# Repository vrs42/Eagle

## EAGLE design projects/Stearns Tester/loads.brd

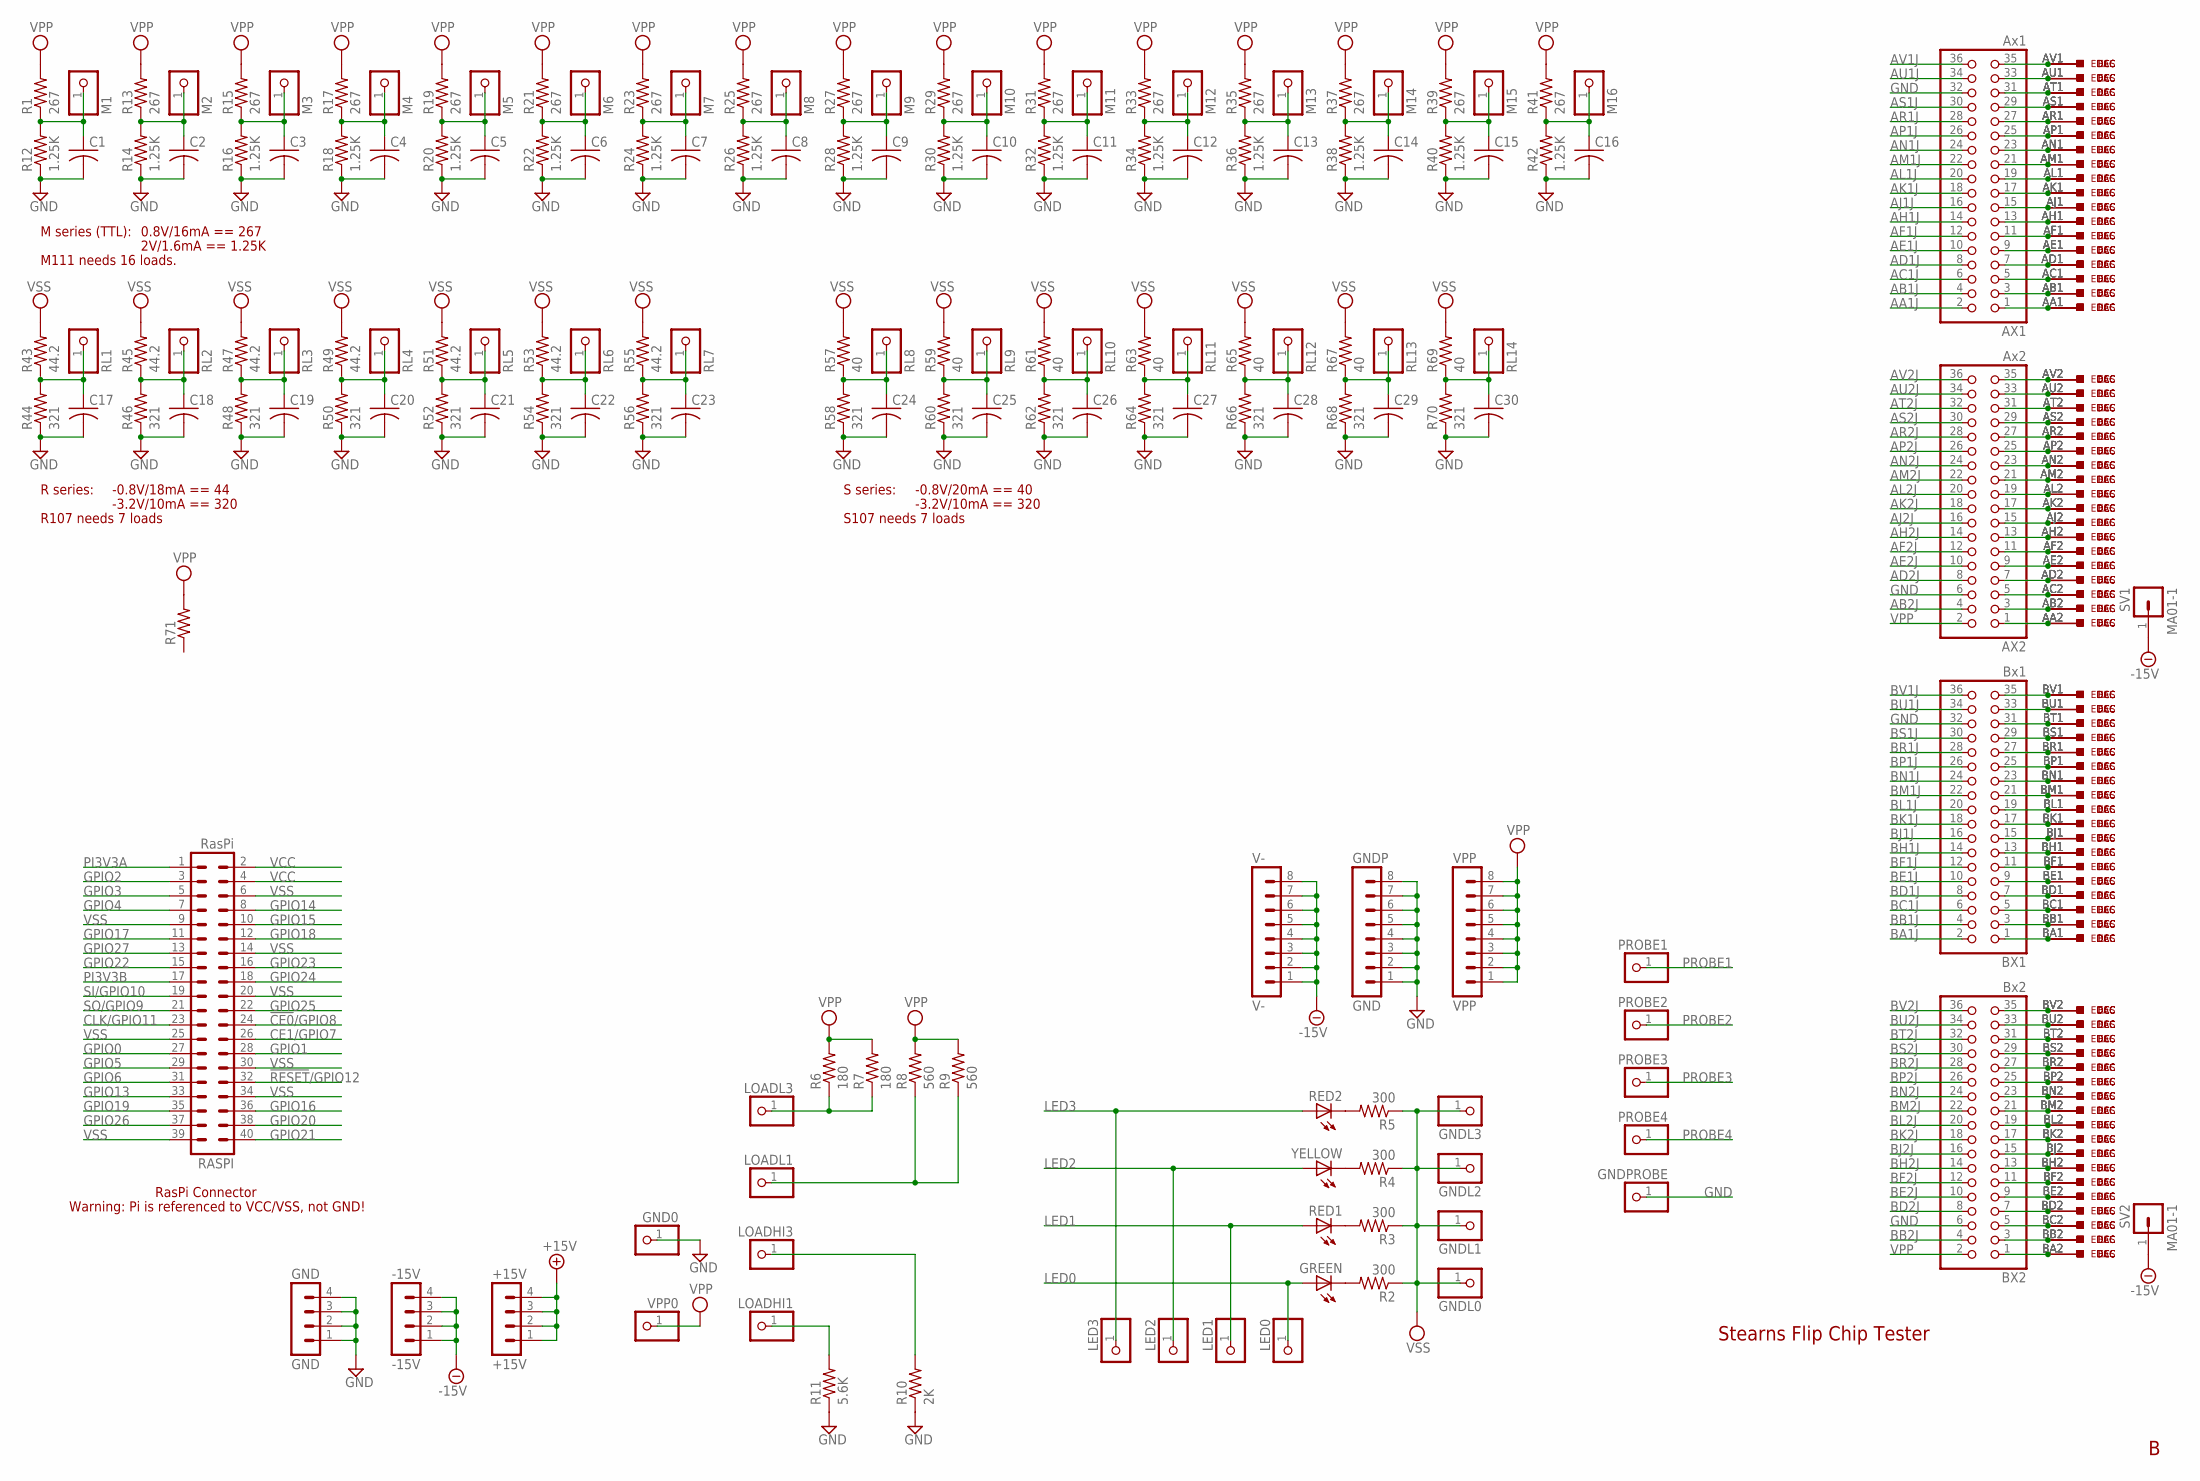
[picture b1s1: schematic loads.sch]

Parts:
+15V: +15V; MA04-1
-15V: -15V; MA04-1
AX1: Ax1; 2X18
AX2: Ax2; 2X18
BX1: Bx1; 2X18
BX2: Bx2; 2X18
C1, C2, C3, C4, C5, C6, C7, C8, C9, C10, C11, C12, C13, C14, C15, C16, C17, C18, C19, C20, C21, C22, C23, C24, C25, C26, C27, C28, C29, C30: C-US025-025X050; C025-025X050
DEC: W971; H807-2
ECS: W971ECS; ECS2418-2
EDAC: W971EDAC; EDAC346-36-2
GND: GND; MA04-1
GND0: PINHD-1X1; 1X01
GNDL0, GNDL1, GNDL2, GNDL3: PINHD-1X1; 1X01
GNDP: GND; MA08-1
GNDPROBE: PINHD-1X1; 1X01
GREEN: LED5MM
LED0, LED1, LED2, LED3: PINHD-1X1; 1X01
LOADHI1, LOADHI3: PINHD-1X1; 1X01
LOADL1, LOADL3: PINHD-1X1; 1X01
M1, M2, M3, M4, M5, M6, M7, M8, M9, M10, M11, M12, M13, M14, M15, M16: PINHD-1X1; 1X01
PROBE1, PROBE2, PROBE3, PROBE4: PINHD-1X1; 1X01
R1, R13, R15, R17, R19, R21, R23, R25, R27, R29, R31, R33, R35, R37, R39, R41: 267; 0207/10
R2, R3, R4, R5: 300; 0207/10
R6, R7: 180; 0207/10
R8, R9: 560; 0207/10
R10: 2K; 0207/10
R11: 5.6K; 0207/10
R12, R14, R16, R18, R20, R22, R24, R26, R28, R30, R32, R34, R36, R38, R40, R42: 1.25K; 0207/10
R43, R45, R47, R49, R51, R53, R55: 44.2; 0207/10
R44, R46, R48, R50, R52, R54, R56, R58, R60, R62, R64, R66, R68, R70: 321; 0207/10
R57, R59, R61, R63, R65, R67, R69: 40; 0207/10
R71: R-US_0207/10; 0207/10
RASPI: RasPi; MA20-2
RED1, RED2: LED5MM
RL1, RL2, RL3, RL4, RL5, RL6, RL7, RL8, RL9, RL10, RL11, RL12, RL13, RL14: PINHD-1X1; 1X01
SV1, SV2: MA01-1
V-: V-; MA08-1
VPP: VPP; MA08-1
VPP0: PINHD-1X1; 1X01
YELLOW: LED5MM

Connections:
!CE0!/GPIO8: RASPI.24
!RESET!/GPIO12: RASPI.32
+15V: +15V.1, +15V.2, +15V.3, +15V.4
-15V: -15V.1, -15V.2, -15V.3, -15V.4, SV1.1, SV2.1, V-.1, V-.2, V-.3, V-.4, V-.5, V-.6, V-.7, V-.8
AA1J: AX1.2
AB1J: AX1.4
AB2J: AX2.4
AC1J: AX1.6
AD1J: AX1.8
AD2J: AX2.8
AE1J: AX1.10
AE2J: AX2.10
AF1J: AX1.12
AF2J: AX2.12
AH1J: AX1.14
AH2J: AX2.14
AJ1J: AX1.16
AJ2J: AX2.16
AK1J: AX1.18
AK2J: AX2.18
AL1J: AX1.20
AL2J: AX2.20
AM1J: AX1.22
AM2J: AX2.22
AN1J: AX1.24
AN2J: AX2.24
AP1J: AX1.26
AP2J: AX2.26
AR1J: AX1.28
AR2J: AX2.28
AS1J: AX1.30
AS2J: AX2.30
AT2J: AX2.32
AU1J: AX1.34
AU2J: AX2.34
AV1J: AX1.36
AV2J: AX2.36
BA1J: BX1.2
BB1J: BX1.4
BB2J: BX2.4
BC1J: BX1.6
BD1J: BX1.8
BD2J: BX2.8
BE1J: BX1.10
BE2J: BX2.10
BF1J: BX1.12
BF2J: BX2.12
BH1J: BX1.14
BH2J: BX2.14
BJ1J: BX1.16
BJ2J: BX2.16
BK1J: BX1.18
BK2J: BX2.18
BL1J: BX1.20
BL2J: BX2.20
BM1J: BX1.22
BM2J: BX2.22
BN1J: BX1.24
BN2J: BX2.24
BP1J: BX1.26
BP2J: BX2.26
BR1J: BX1.28
BR2J: BX2.28
BS1J: BX1.30
BS2J: BX2.30
BT2J: BX2.32
BU1J: BX1.34
BU2J: BX2.34
BV1J: BX1.36
BV2J: BX2.36
CE1/GPIO7: RASPI.26
CLK/GPIO11: RASPI.23
GND: AX1.32, AX2.6, BX1.32, BX2.6, C1.2, C2.2, C3.2, C4.2, C5.2, C6.2, C7.2, C8.2, C9.2, C10.2, C11.2, C12.2, C13.2, C14.2, C15.2, C16.2, C17.2, C18.2, C19.2, C20.2, C21.2, C22.2, C23.2, C24.2, C25.2, C26.2, C27.2, C28.2, C29.2, C30.2, GND.1, GND.2, GND.3, GND.4, GND0.1, GNDP.1, GNDP.2, GNDP.3, GNDP.4, GNDP.5, GNDP.6, GNDP.7, GNDP.8, GNDPROBE.1, R10.1, R11.1, R12.1, R14.1, R16.1, R18.1, R20.1, R22.1, R24.1, R26.1, R28.1, R30.1, R32.1, R34.1, R36.1, R38.1, R40.1, R42.1, R44.1, R46.1, R48.1, R50.1, R52.1, R54.1, R56.1, R58.1, R60.1, R62.1, R64.1, R66.1, R68.1, R70.1
GPIO0: RASPI.27
GPIO1: RASPI.28
GPIO2: RASPI.3
GPIO3: RASPI.5
GPIO4: RASPI.7
GPIO5: RASPI.29
GPIO6: RASPI.31
GPIO13: RASPI.33
GPIO14: RASPI.8
GPIO15: RASPI.10
GPIO16: RASPI.36
GPIO17: RASPI.11
GPIO18: RASPI.12
GPIO19: RASPI.35
GPIO20: RASPI.38
GPIO21: RASPI.40
GPIO22: RASPI.15
GPIO23: RASPI.16
GPIO24: RASPI.18
GPIO25: RASPI.22
GPIO26: RASPI.37
GPIO27: RASPI.13
LED0: GREEN.A, LED0.1
LED1: LED1.1, RED1.A
LED2: LED2.1, YELLOW.A
LED3: LED3.1, RED2.A
unnamed: AX1.1, DEC.AA1, ECS.AA1, EDAC.AA1
unnamed: AX1.35, DEC.AV1, ECS.AV1, EDAC.AV1
unnamed: AX1.33, DEC.AU1, ECS.AU1, EDAC.AU1
unnamed: AX1.31, DEC.AT1, ECS.AT1, EDAC.AT1
unnamed: AX1.29, DEC.AS1, ECS.AS1, EDAC.AS1
unnamed: AX1.27, DEC.AR1, ECS.AR1, EDAC.AR1
unnamed: AX1.25, DEC.AP1, ECS.AP1, EDAC.AP1
unnamed: AX1.23, DEC.AN1, ECS.AN1, EDAC.AN1
unnamed: AX1.21, DEC.AM1, ECS.AM1, EDAC.AM1
unnamed: AX1.19, DEC.AL1, ECS.AL1, EDAC.AL1
unnamed: AX1.17, DEC.AK1, ECS.AK1, EDAC.AK1
unnamed: AX1.15, DEC.AJ1, ECS.AJ1, EDAC.AJ1
unnamed: AX1.13, DEC.AH1, ECS.AH1, EDAC.AH1
unnamed: AX1.11, DEC.AF1, ECS.AF1, EDAC.AF1
unnamed: AX1.9, DEC.AE1, ECS.AE1, EDAC.AE1
unnamed: AX1.7, DEC.AD1, ECS.AD1, EDAC.AD1
unnamed: AX1.5, DEC.AC1, ECS.AC1, EDAC.AC1
unnamed: AX1.3, DEC.AB1, ECS.AB1, EDAC.AB1
unnamed: AX2.1, DEC.AA2, ECS.AA2, EDAC.AA2
unnamed: AX2.3, DEC.AB2, ECS.AB2, EDAC.AB2
unnamed: AX2.5, DEC.AC2, ECS.AC2, EDAC.AC2
unnamed: AX2.7, DEC.AD2, ECS.AD2, EDAC.AD2
unnamed: AX2.9, DEC.AE2, ECS.AE2, EDAC.AE2
unnamed: AX2.11, DEC.AF2, ECS.AF2, EDAC.AF2
unnamed: AX2.13, DEC.AH2, ECS.AH2, EDAC.AH2
unnamed: AX2.15, DEC.AJ2, ECS.AJ2, EDAC.AJ2
unnamed: AX2.17, DEC.AK2, ECS.AK2, EDAC.AK2
unnamed: AX2.19, DEC.AL2, ECS.AL2, EDAC.AL2
unnamed: AX2.21, DEC.AM2, ECS.AM2, EDAC.AM2
unnamed: AX2.23, DEC.AN2, ECS.AN2, EDAC.AN2
unnamed: AX2.25, DEC.AP2, ECS.AP2, EDAC.AP2
unnamed: AX2.27, DEC.AR2, ECS.AR2, EDAC.AR2
unnamed: AX2.29, DEC.AS2, ECS.AS2, EDAC.AS2
unnamed: AX2.31, DEC.AT2, ECS.AT2, EDAC.AT2
unnamed: AX2.33, DEC.AU2, ECS.AU2, EDAC.AU2
unnamed: AX2.35, DEC.AV2, ECS.AV2, EDAC.AV2
unnamed: BX2.1, DEC.BA2, ECS.BA2, EDAC.BA2
unnamed: BX2.3, DEC.BB2, ECS.BB2, EDAC.BB2
unnamed: BX2.5, DEC.BC2, ECS.BC2, EDAC.BC2
unnamed: BX2.7, DEC.BD2, ECS.BD2, EDAC.BD2
unnamed: BX2.9, DEC.BE2, ECS.BE2, EDAC.BE2
unnamed: BX2.11, DEC.BF2, ECS.BF2, EDAC.BF2
unnamed: BX2.13, DEC.BH2, ECS.BH2, EDAC.BH2
unnamed: BX2.15, DEC.BJ2, ECS.BJ2, EDAC.BJ2
unnamed: BX2.17, DEC.BK2, ECS.BK2, EDAC.BK2
unnamed: BX2.19, DEC.BL2, ECS.BL2, EDAC.BL2
unnamed: BX2.21, DEC.BM2, ECS.BM2, EDAC.BM2
unnamed: BX2.23, DEC.BN2, ECS.BN2, EDAC.BN2
unnamed: BX2.25, DEC.BP2, ECS.BP2, EDAC.BP2
unnamed: BX2.27, DEC.BR2, ECS.BR2, EDAC.BR2
unnamed: BX2.29, DEC.BS2, ECS.BS2, EDAC.BS2
unnamed: BX2.31, DEC.BT2, ECS.BT2, EDAC.BT2
unnamed: BX2.33, DEC.BU2, ECS.BU2, EDAC.BU2
unnamed: BX2.35, DEC.BV2, ECS.BV2, EDAC.BV2
unnamed: BX1.1, DEC.BA1, ECS.BA1, EDAC.BA1
unnamed: BX1.3, DEC.BB1, ECS.BB1, EDAC.BB1
unnamed: BX1.5, DEC.BC1, ECS.BC1, EDAC.BC1
unnamed: BX1.7, DEC.BD1, ECS.BD1, EDAC.BD1
unnamed: BX1.9, DEC.BE1, ECS.BE1, EDAC.BE1
unnamed: BX1.11, DEC.BF1, ECS.BF1, EDAC.BF1
unnamed: BX1.13, DEC.BH1, ECS.BH1, EDAC.BH1
unnamed: BX1.15, DEC.BJ1, ECS.BJ1, EDAC.BJ1
unnamed: BX1.17, DEC.BK1, ECS.BK1, EDAC.BK1
unnamed: BX1.19, DEC.BL1, ECS.BL1, EDAC.BL1
unnamed: BX1.21, DEC.BM1, ECS.BM1, EDAC.BM1
unnamed: BX1.23, DEC.BN1, ECS.BN1, EDAC.BN1
unnamed: BX1.25, DEC.BP1, ECS.BP1, EDAC.BP1
unnamed: BX1.27, DEC.BR1, ECS.BR1, EDAC.BR1
unnamed: BX1.29, DEC.BS1, ECS.BS1, EDAC.BS1
unnamed: BX1.31, DEC.BT1, ECS.BT1, EDAC.BT1
unnamed: BX1.33, DEC.BU1, ECS.BU1, EDAC.BU1
unnamed: BX1.35, DEC.BV1, ECS.BV1, EDAC.BV1
unnamed: GREEN.K (C), R2.2
unnamed: R3.2, RED1.K (C)
unnamed: R4.2, YELLOW.K (C)
unnamed: R5.2, RED2.K (C)
unnamed: LOADL3.1, R6.1, R7.1
unnamed: LOADL1.1, R8.1, R9.1
unnamed: LOADHI1.1, R11.2
unnamed: LOADHI3.1, R10.2
unnamed: C1.1, M1.1, R1.1, R12.2
unnamed: C2.1, M2.1, R13.1, R14.2
unnamed: C3.1, M3.1, R15.1, R16.2
unnamed: C4.1, M4.1, R17.1, R18.2
unnamed: C5.1, M5.1, R19.1, R20.2
unnamed: C6.1, M6.1, R21.1, R22.2
unnamed: C7.1, M7.1, R23.1, R24.2
unnamed: C8.1, M8.1, R25.1, R26.2
unnamed: C9.1, M9.1, R27.1, R28.2
unnamed: C10.1, M10.1, R29.1, R30.2
unnamed: C11.1, M11.1, R31.1, R32.2
unnamed: C12.1, M12.1, R33.1, R34.2
unnamed: C13.1, M13.1, R35.1, R36.2
unnamed: C14.1, M14.1, R37.1, R38.2
unnamed: C15.1, M15.1, R39.1, R40.2
unnamed: C16.1, M16.1, R41.1, R42.2
unnamed: C17.1, R43.1, R44.2, RL1.1
unnamed: C18.1, R45.1, R46.2, RL2.1
unnamed: C19.1, R47.1, R48.2, RL3.1
unnamed: C20.1, R49.1, R50.2, RL4.1
unnamed: C21.1, R51.1, R52.2, RL5.1
unnamed: C22.1, R53.1, R54.2, RL6.1
unnamed: C23.1, R55.1, R56.2, RL7.1
unnamed: C24.1, R57.1, R58.2, RL8.1
unnamed: C25.1, R59.1, R60.2, RL9.1
unnamed: C26.1, R61.1, R62.2, RL10.1
unnamed: C27.1, R63.1, R64.2, RL11.1
unnamed: C28.1, R65.1, R66.2, RL12.1
unnamed: C29.1, R67.1, R68.2, RL13.1
unnamed: C30.1, R69.1, R70.2, RL14.1
PI3V3A: RASPI.1
PI3V3B: RASPI.17
PROBE1: PROBE1.1
PROBE2: PROBE2.1
PROBE3: PROBE3.1
PROBE4: PROBE4.1
SI/GPIO10: RASPI.19
SO/GPIO9: RASPI.21
VCC: RASPI.2, RASPI.4
VPP: AX2.2, BX2.2, R1.2, R6.2, R7.2, R8.2, R9.2, R13.2, R15.2, R17.2, R19.2, R21.2, R23.2, R25.2, R27.2, R29.2, R31.2, R33.2, R35.2, R37.2, R39.2, R41.2, R71.2, VPP.1, VPP.2, VPP.3, VPP.4, VPP.5, VPP.6, VPP.7, VPP.8, VPP0.1
VSS: GNDL0.1, GNDL1.1, GNDL2.1, GNDL3.1, R2.1, R3.1, R4.1, R5.1, R43.2, R45.2, R47.2, R49.2, R51.2, R53.2, R55.2, R57.2, R59.2, R61.2, R63.2, R65.2, R67.2, R69.2, RASPI.6, RASPI.9, RASPI.14, RASPI.20, RASPI.25, RASPI.30, RASPI.34, RASPI.39

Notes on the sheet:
Stearns Flip Chip Tester
RasPi Connector
Warning: Pi is referenced to VCC/VSS, not GND!
M series (TTL):
2V/1.6mA == 1.25K
0.8V/16mA == 267
M111 needs 16 loads.
R series:
R107 needs 7 loads
-0.8V/18mA == 44
-3.2V/10mA == 320
S series:
S107 needs 7 loads
-0.8V/20mA == 40

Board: 2 copper layers, 170 parts (0 on the bottom side), 120 nets, no tracks yet.

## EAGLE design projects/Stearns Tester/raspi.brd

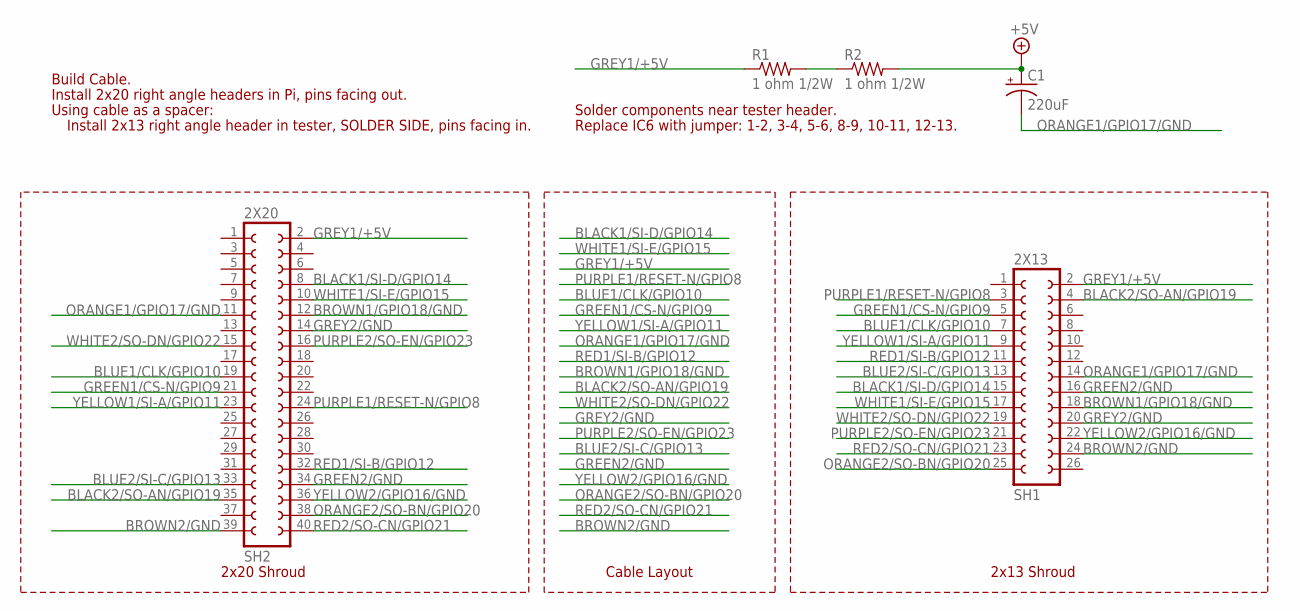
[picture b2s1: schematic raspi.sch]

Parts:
C1: 220uF; E15-6
R1, R2: 1 ohm 1/2W; 0207/10
SH1: 2X13; FE13-2
SH2: 2X20; FE20-2

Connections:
+5V: C1.+, R2.2
BLACK1/SI-D/GPIO14: SH1.15, SH2.8
BLACK2/SO-AN/GPIO19: SH1.4, SH2.35
BLUE1/CLK/GPIO10: SH1.7, SH2.19
BLUE2/SI-C/GPIO13: SH1.13, SH2.33
BROWN1/GPIO18/GND: SH1.18, SH2.12
BROWN2/GND: SH1.24, SH2.39
GREEN1/CS-N/GPIO9: SH1.5, SH2.21
GREEN2/GND: SH1.16, SH2.34
GREY1/+5V: R1.1, SH1.2, SH2.2
GREY2/GND: SH1.20, SH2.14
unnamed: R1.2, R2.1
ORANGE1/GPIO17/GND: C1.-, SH1.14, SH2.11
ORANGE2/SO-BN/GPIO20: SH1.25, SH2.38
PURPLE1/RESET-N/GPIO8: SH1.3, SH2.24
PURPLE2/SO-EN/GPIO23: SH1.21, SH2.16
RED1/SI-B/GPIO12: SH1.11, SH2.32
RED2/SO-CN/GPIO21: SH1.23, SH2.40
WHITE1/SI-E/GPIO15: SH1.17, SH2.10
WHITE2/SO-DN/GPIO22: SH1.19, SH2.15
YELLOW1/SI-A/GPIO11: SH1.9, SH2.23
YELLOW2/GPIO16/GND: SH1.22, SH2.36

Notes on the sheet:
Replace IC6 with jumper: 1-2, 3-4, 5-6, 8-9, 10-11, 12-13.
Cable Layout
2x20 Shroud
2x13 Shroud
Solder components near tester header.
Build Cable.
Using cable as a spacer:
Install 2x13 right angle header in tester, SOLDER SIDE, pins facing in.
Install 2x20 right angle headers in Pi, pins facing out.

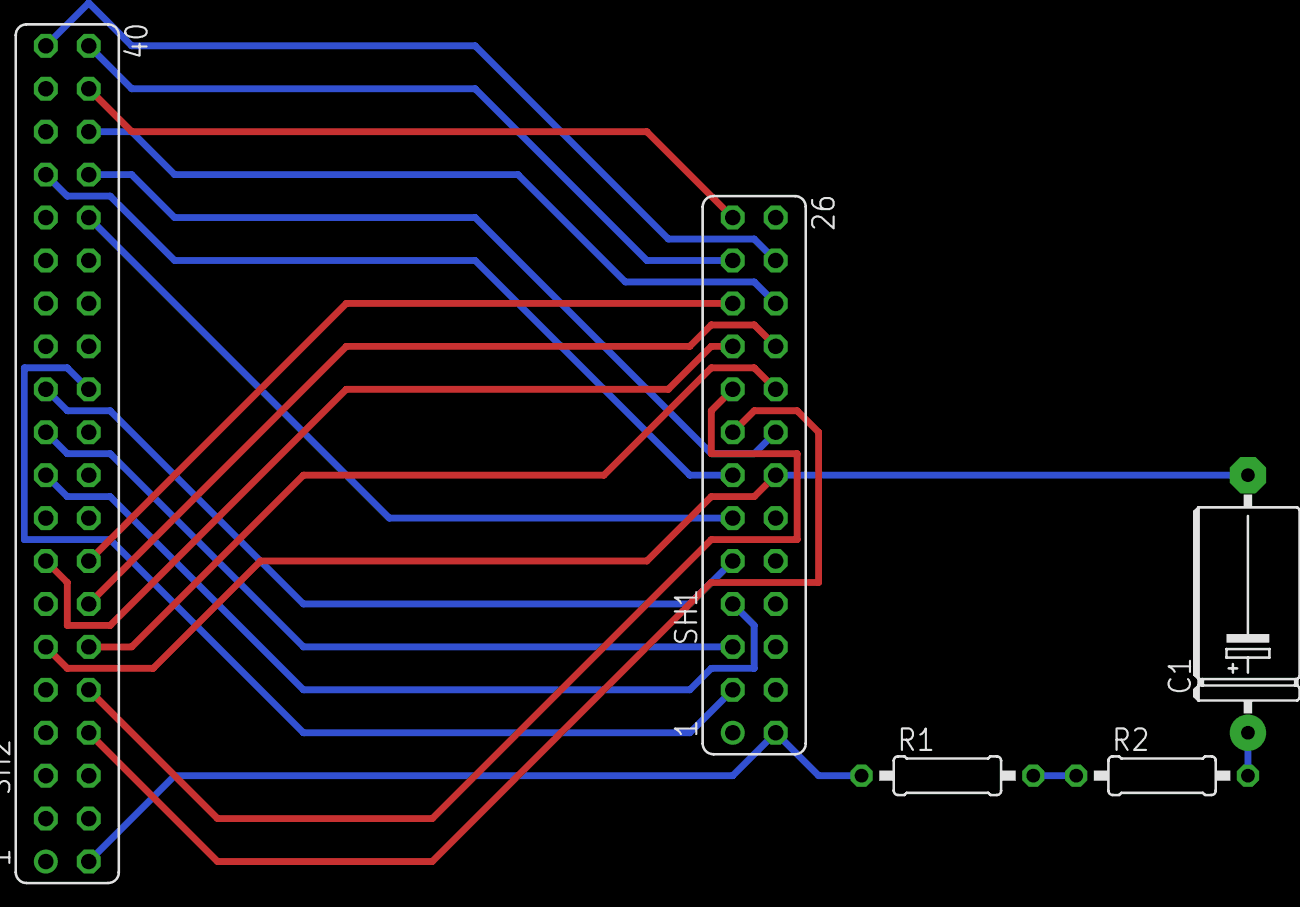
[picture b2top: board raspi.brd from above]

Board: 3 copper layers, 5 parts (0 on the bottom side), 22 nets.

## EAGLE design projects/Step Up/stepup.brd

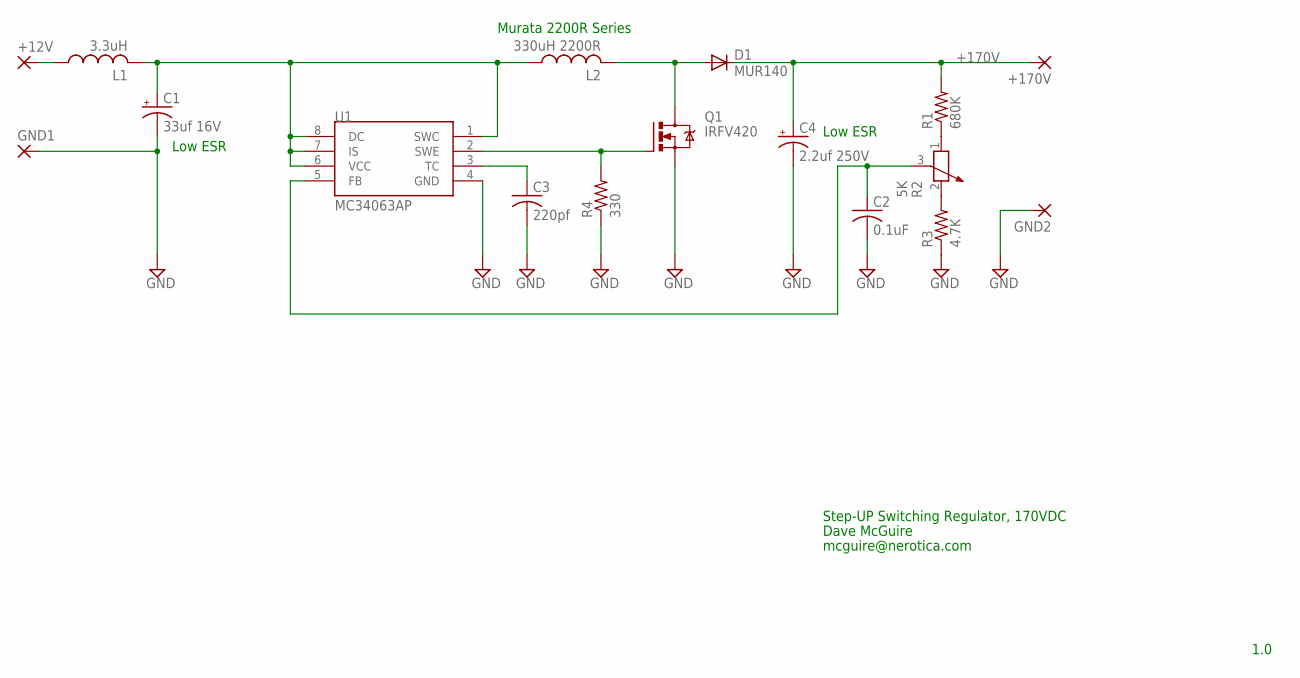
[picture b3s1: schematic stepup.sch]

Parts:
+12V, +170V: 2,54/0,9
C1: 33uf 16V; E2,5-6E
C2: 0.1uF; C050-025X075
C3: 220pf; C050-025X075
C4: 2.2uf 250V; E2,5-6E
D1: MUR140; DO41-10
GND1, GND2: 2,54/0,9
L1: 3.3uH; 0207/10
L2: 330uH 2200R; 0207/10
Q1: IRFV420; TO220BV
R1: 680K; 0207/10
R2: 5K; PT-10S
R3: 4.7K; 0207/10
R4: 330; 0207/10
U1: MC34063AP; DIL08

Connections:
+170V: +170V.1, C4.+, D1.C, R1.2
GND: C1.-, C2.2, C3.2, C4.-, GND1.1, GND2.1, Q1.S, R3.1, R4.1, U1.4 (GND)
unnamed: C1.+, L1.2, L2.1, U1.1 (SWC), U1.6 (VCC), U1.7 (IS), U1.8 (DC)
unnamed: C3.1, U1.3 (TC)
unnamed: Q1.G, R4.2, U1.2 (SWE)
unnamed: C2.1, R2.3, U1.5 (FB)
unnamed: D1.A, L2.2, Q1.D
unnamed: R2.2, R3.2
unnamed: R1.1, R2.1
unnamed: +12V.1, L1.1

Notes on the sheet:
Low ESR
Murata 2200R Series
Step-UP Switching Regulator, 170VDC
1.0
Dave McGuire
mcguire@nerotica.com

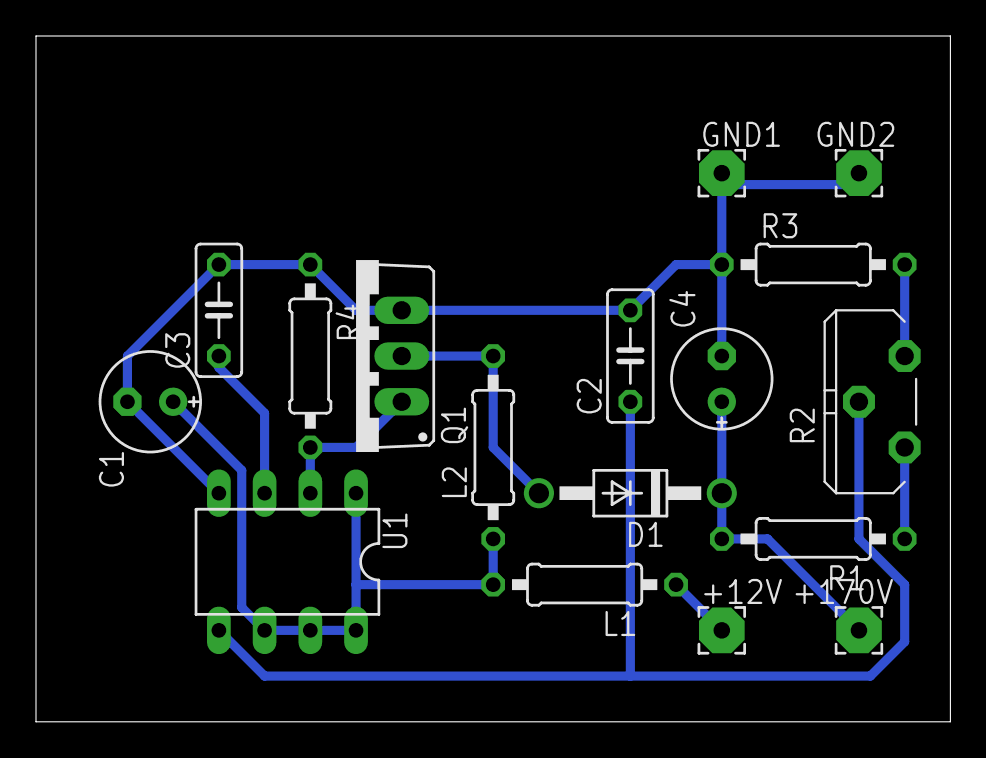
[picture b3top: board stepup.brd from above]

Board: 2 copper layers, 50.8 x 38.1 mm, 17 parts (0 on the bottom side), 10 nets.

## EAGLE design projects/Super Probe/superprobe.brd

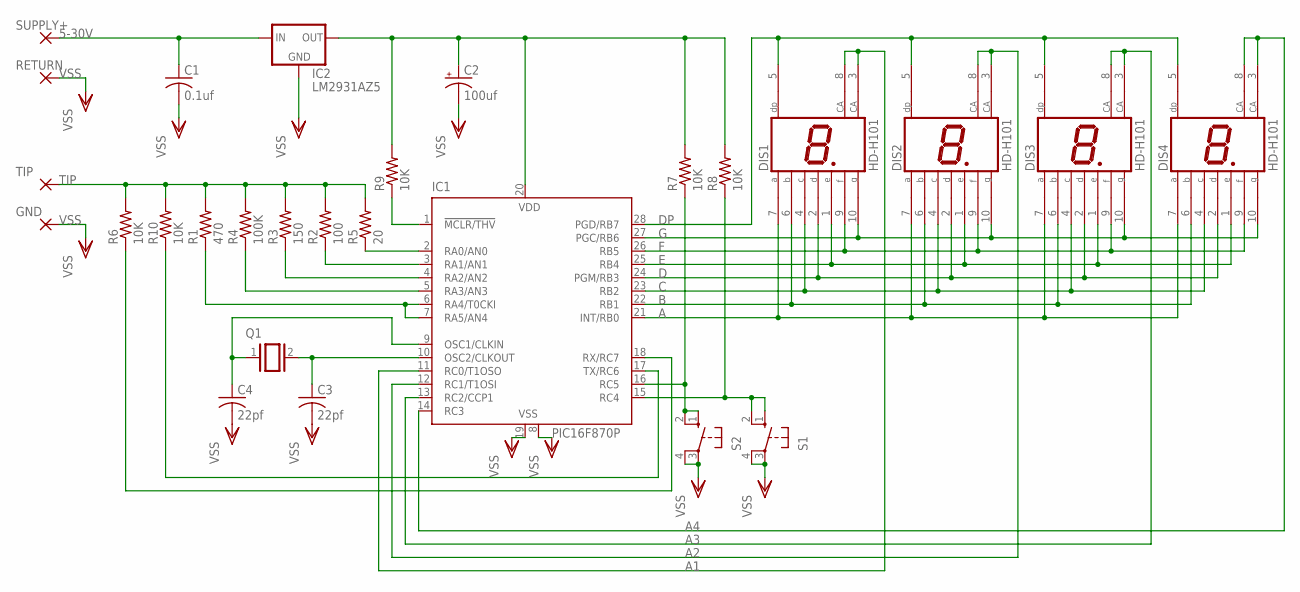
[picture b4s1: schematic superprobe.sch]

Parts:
C1: 0.1uf; C050-025X075
C2: 100uf; E15-6
C3, C4: 22pf; C050-025X075
DIS1, DIS2, DIS3, DIS4: HD-H101; HDSP-M
GND: PAD-0520; 0520
IC1: PIC16F870P; DIL28-3
IC2: LM2931AZ5; TO92
Q1: XTAL/S; QS
R1: 470; 0207/10
R2: 100; 0207/10
R3: 150; 0207/10
R4: 100K; 0207/10
R5: 20; 0207/10
R6, R7, R8, R9, R10: 10K; 0207/10
RETURN: PAD-0520; 0520
S1, S2: 40-XX; B3F-40XX
SUPPLY+: PAD-0520; 0520
TIP: PAD-0520; 0520

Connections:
5-30V: C1.1, IC2.1 (IN), SUPPLY+.P$1
A: DIS1.7 (A), DIS2.7 (A), DIS3.7 (A), DIS4.7 (A), IC1.21 (INT/RB0)
A1: DIS1.3 (CA), DIS1.8 (CA), IC1.11 (RC0/T1OSO)
A2: DIS2.3 (CA), DIS2.8 (CA), IC1.12 (RC1/T1OSI)
A3: DIS3.3 (CA), DIS3.8 (CA), IC1.13 (RC2/CCP1)
A4: DIS4.3 (CA), DIS4.8 (CA), IC1.14 (RC3)
B: DIS1.6 (B), DIS2.6 (B), DIS3.6 (B), DIS4.6 (B), IC1.22 (RB1)
C: DIS1.4 (C), DIS2.4 (C), DIS3.4 (C), DIS4.4 (C), IC1.23 (RB2)
D: DIS1.2 (D), DIS2.2 (D), DIS3.2 (D), DIS4.2 (D), IC1.24 (PGM/RB3)
DP: DIS1.5 (DP), DIS2.5 (DP), DIS3.5 (DP), DIS4.5 (DP), IC1.28 (PGD/RB7)
E: DIS1.1 (E), DIS2.1 (E), DIS3.1 (E), DIS4.1 (E), IC1.25 (RB4)
F: DIS1.9 (F), DIS2.9 (F), DIS3.9 (F), DIS4.9 (F), IC1.26 (RB5)
G: DIS1.10 (G), DIS2.10 (G), DIS3.10 (G), DIS4.10 (G), IC1.27 (PGC/RB6)
unnamed: IC1.1 (!MCLR/THV), R9.1
unnamed: IC1.2 (RA0/AN0), R5.1
unnamed: IC1.6 (RA4/T0CKI), IC1.7 (RA5/AN4), R1.1
unnamed: IC1.5 (RA3/AN3), R4.1
unnamed: IC1.4 (RA2/AN2), R3.1
unnamed: IC1.3 (RA1/AN1), R2.1
unnamed: IC1.16 (RC5), R7.1, S2.1 (S), S2.2 (S1)
unnamed: IC1.15 (RC4), R8.1, S1.1 (S), S1.2 (S1)
unnamed: IC1.18 (RX/RC7), R6.1
unnamed: IC1.17 (TX/RC6), R10.1
unnamed: C4.1, IC1.9 (OSC1/CLKIN), Q1.1
unnamed: C3.1, IC1.10 (OSC2/CLKOUT), Q1.2
TIP: R1.2, R2.2, R3.2, R4.2, R5.2, R6.2, R10.2, TIP.P$1
VDD: C2.+, IC1.20 (VDD), IC2.3 (OUT), R7.2, R8.2, R9.2
VSS: C1.2, C2.-, C3.2, C4.2, GND.P$1, IC1.8 (VSS), IC1.19 (VSS), IC2.2 (GND), RETURN.P$1, S1.3, S1.4 (P1), S2.3, S2.4 (P1)

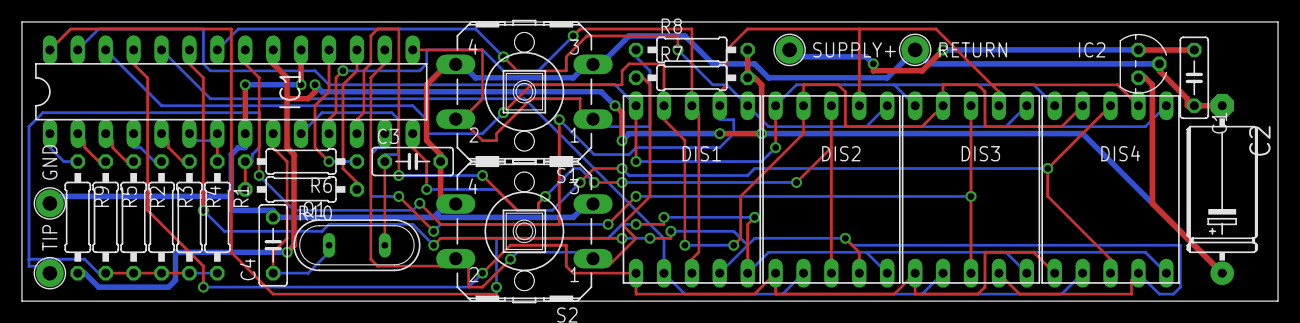
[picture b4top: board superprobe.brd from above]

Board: 2 copper layers, 114.3 x 25.4 mm, 27 parts (0 on the bottom side), 28 nets.

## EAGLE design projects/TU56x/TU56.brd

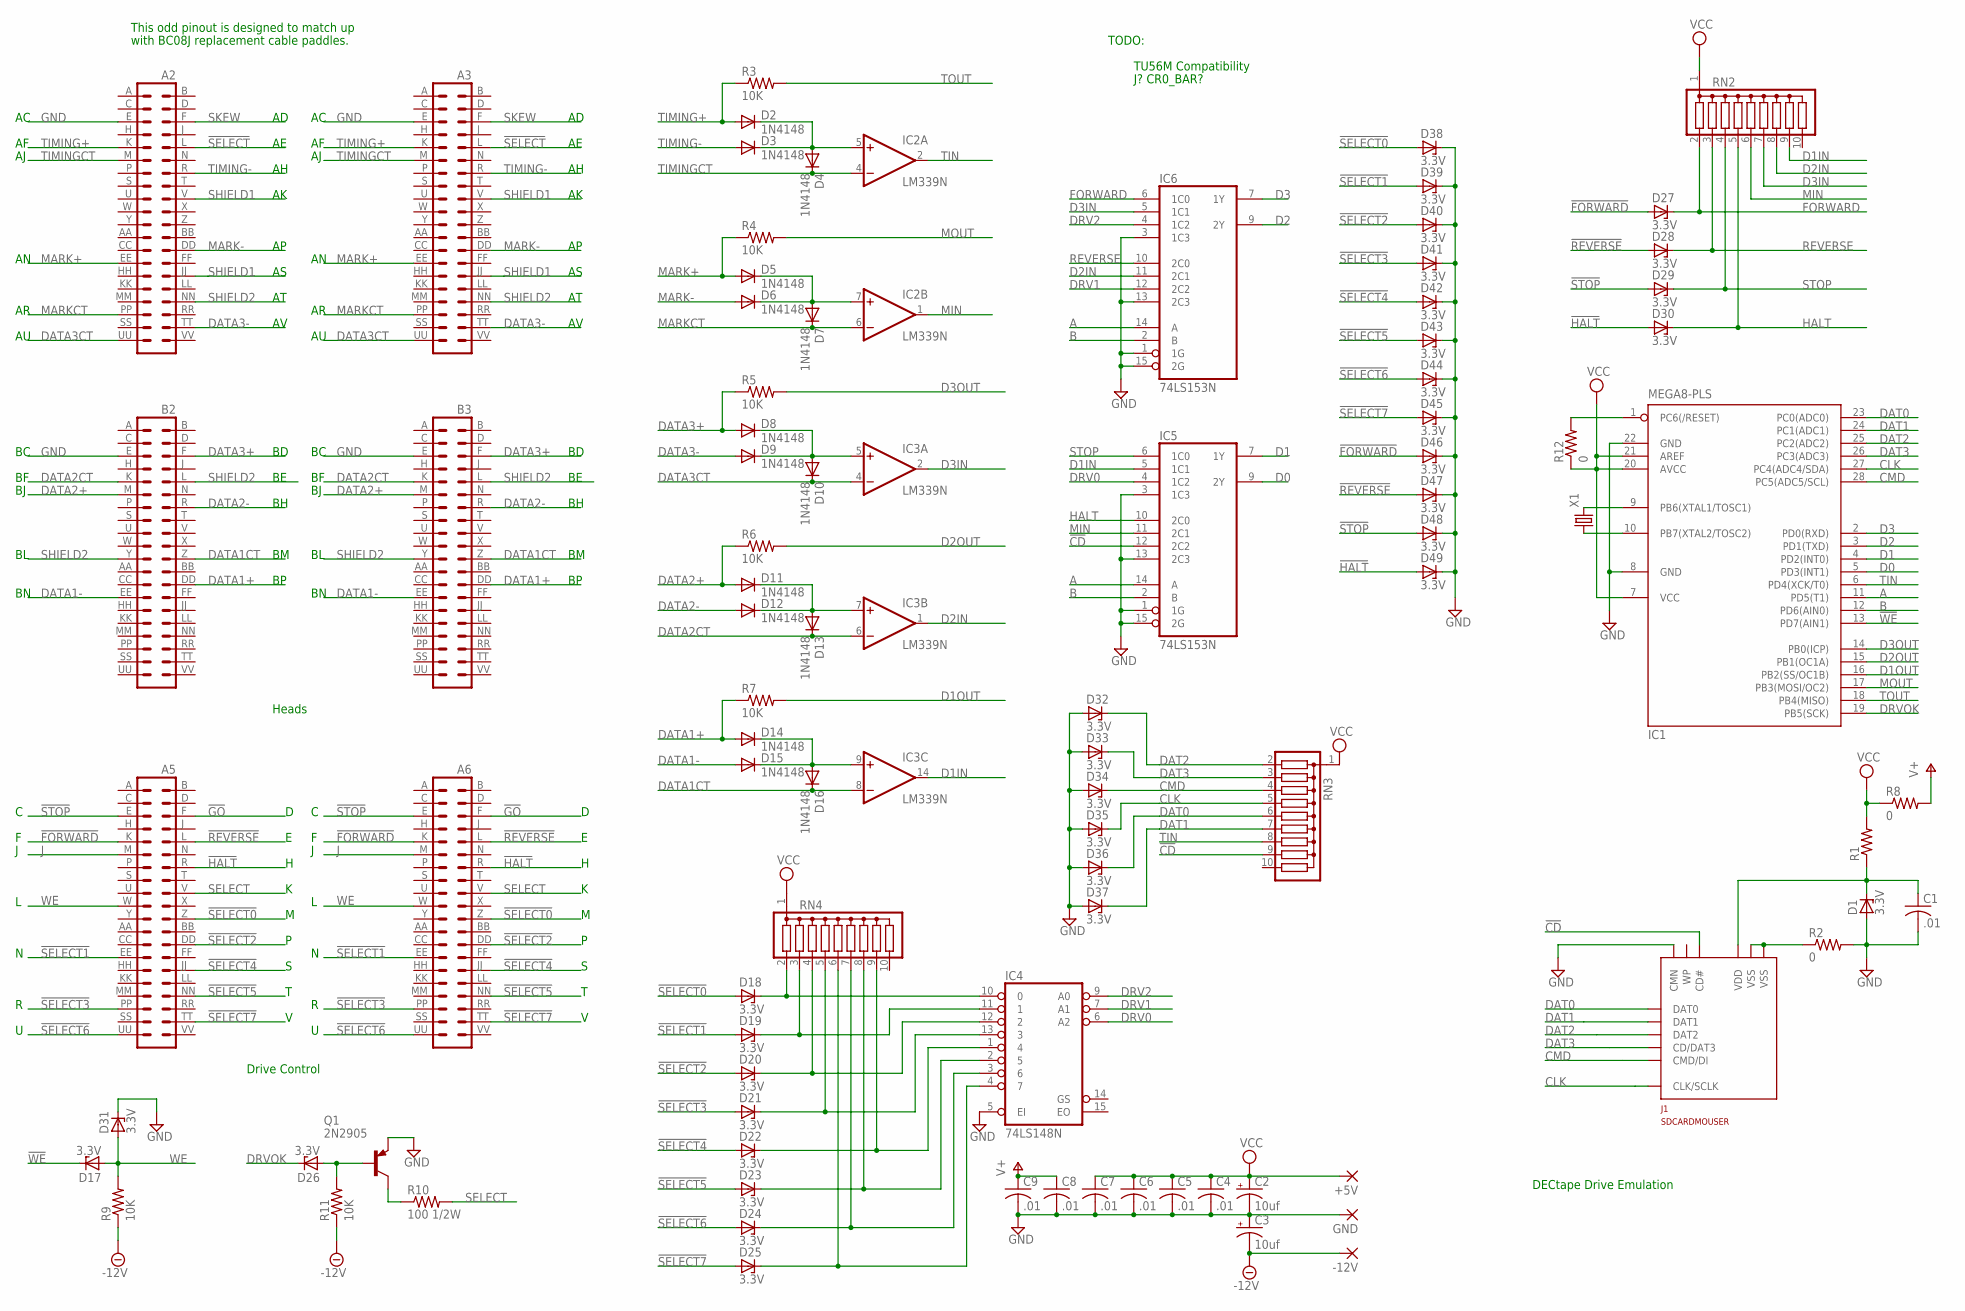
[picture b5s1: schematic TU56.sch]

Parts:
+5V: 2,15/1,0
-12V: 2,15/1,0
A2, A3, A5, A6: DEC40PINV
B2, B3: DEC40PINV
C1, C4, C5, C6, C7, C8, C9: .01; C050-025X075
C2, C3: 10uf; E2,5-7
D1, D17, D18, D19, D20, D21, D22, D23, D24, D25, D26, D27, D28, D29, D30, D31, D32, D33, D34, D35, D36, D37, D38, D39, D40, D41, D42, D43, D44, D45, D46, D47, D48, D49: 3.3V; DO35Z10
D2, D3, D4, D5, D6, D7, D8, D9, D10, D11, D12, D13, D14, D15, D16: 1N4148; DO35-10
GND: 2,15/1,0
IC1: MEGA8-PLS; DIL28-3
IC2, IC3: LM339N; DIL14
IC4: 74LS148N; DIL16
IC5, IC6: 74LS153N; DIL16
J1: SDCARDMOUSER; SCDA1A
Q1: 2N2905; TO5
R1: R-US_0207/10; 0207/10
R2, R8, R12: 0; 0207/10
R3, R4, R5, R6, R7, R9, R11: 10K; 0207/10
R10: 100 1/2W; 0309V
RN2, RN3, RN4: G09R; SIL10
X1: CRYSTALHC49S; HC49/S

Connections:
!CD: IC5.12 (2C2), J1.10 (CD#), RN3.9
!FORWARD: A5.K (9), A6.K (9), D27.A, D46.A
!GO: A5.F (6), A6.F (6)
!HALT: A5.R (14), A6.R (14), D30.A, D49.A
!REVERSE: A5.L (10), A6.L (10), D28.A, D47.A
!SELECT: A2.L (10), A3.L (10)
!SELECT0: A5.Z (22), A6.Z (22), D18.A, D38.A
!SELECT1: A5.EE (27), A6.EE (27), D19.A, D39.A
!SELECT2: A5.DD (26), A6.DD (26), D20.A, D40.A
!SELECT3: A5.PP (35), A6.PP (35), D21.A, D41.A
!SELECT4: A5.JJ (30), A6.JJ (30), D22.A, D42.A
!SELECT5: A5.NN (34), A6.NN (34), D23.A, D43.A
!SELECT6: A5.UU (39), A6.UU (39), D24.A, D44.A
!SELECT7: A5.TT (38), A6.TT (38), D25.A, D45.A
!STOP: A5.E (5), A6.E (5), D29.A, D48.A
!WE: D17.C, IC1.13 (PD7(AIN1))
-12V: -12V.1, C3.-, R9.1, R11.1
A: IC1.11 (PD5(T1)), IC5.14 (A), IC6.14 (A)
B: IC1.12 (PD6(AIN0)), IC5.2 (B), IC6.2 (B)
CLK: D35.C, IC1.27 (PC4(ADC4/SDA)), J1.5 (CLK/SCLK), RN3.5
CMD: D34.C, IC1.28 (PC5(ADC5/SCL)), J1.2 (CMD/DI), RN3.4
D0: IC1.5 (PD3(INT1)), IC5.9 (2Y)
D1: IC1.4 (PD2(INT0)), IC5.7 (1Y)
D1IN: IC3.14 (OUT), IC5.5 (1C1), RN2.9
D1OUT: IC1.16 (PB2(SS/OC1B)), R7.2
D2: IC1.3 (PD1(TXD)), IC6.9 (2Y)
D2IN: IC3.1 (OUT), IC6.11 (2C1), RN2.8
D2OUT: IC1.15 (PB1(OC1A)), R6.2
D3: IC1.2 (PD0(RXD)), IC6.7 (1Y)
D3IN: IC3.2 (OUT), IC6.5 (1C1), RN2.7
D3OUT: IC1.14 (PB0(ICP)), R5.2
DAT0: D36.C, IC1.23 (PC0(ADC0)), J1.7 (DAT0), RN3.6
DAT1: D37.C, IC1.24 (PC1(ADC1)), J1.8 (DAT1), RN3.7
DAT2: D32.C, IC1.25 (PC2(ADC2)), J1.9 (DAT2), RN3.2
DAT3: D33.C, IC1.26 (PC3(ADC3)), J1.1 (CD/DAT3), RN3.3
DATA1+: B2.DD (26), B3.DD (26), D14.A, R7.1
DATA1-: B2.EE (27), B3.EE (27), D15.A
DATA1CT: B2.Z (22), B3.Z (22), D16.C, IC3.8 (-IN)
DATA2+: B2.M (11), B3.M (11), D11.A, R6.1
DATA2-: B2.R (14), B3.R (14), D12.A
DATA2CT: B2.K (9), B3.K (9), D13.C, IC3.6 (-IN)
DATA3+: B2.F (6), B3.F (6), D8.A, R5.1
DATA3-: A2.TT (38), A3.TT (38), D9.A
DATA3CT: A2.UU (39), A3.UU (39), D10.C, IC3.4 (-IN)
DRV0: IC4.6 (A2), IC5.4 (1C2)
DRV1: IC4.7 (A1), IC6.12 (2C2)
DRV2: IC4.9 (A0), IC6.4 (1C2)
DRVOK: D26.C, IC1.19 (PB5(SCK))
FORWARD: D27.C, IC6.6 (1C0), RN2.2
GND: A2.E (5), A3.E (5), B2.E (5), B3.E (5), C1.2, C2.-, C3.+, C4.2, C5.2, C6.2, C7.2, C8.2, C9.2, D1.A, D31.C, D32.A, D33.A, D34.A, D35.A, D36.A, D37.A, D38.C, D39.C, D40.C, D41.C, D42.C, D43.C, D44.C, D45.C, D46.C, D47.C, D48.C, D49.C, GND.1, IC1.8 (GND), IC1.22 (GND), IC2.12 (GND), IC3.12 (GND), IC4.5 (EI), IC4.8 (GND), IC5.1 (1G), IC5.3 (1C3), IC5.8 (GND), IC5.13 (2C3), IC5.15 (2G), IC6.1 (1G), IC6.3 (1C3), IC6.8 (GND), IC6.13 (2C3), IC6.15 (2G), J1.11 (CMN), J1.13 (GND), J1.14 (GND), Q1.1 (E), R2.2
HALT: D30.C, IC5.10 (2C0), RN2.5
J: A5.M (11), A6.M (11)
MARK+: A2.EE (27), A3.EE (27), D5.A, R4.1
MARK-: A2.DD (26), A3.DD (26), D6.A
MARKCT: A2.PP (35), A3.PP (35), D7.C, IC2.6 (-IN)
MIN: IC2.1 (OUT), IC5.11 (2C1), RN2.6
MOUT: IC1.17 (PB3(MOSI/OC2)), R4.2
unnamed: IC1.10 (PB7(XTAL2/TOSC2)), X1.1
unnamed: IC1.9 (PB6(XTAL1/TOSC1)), X1.2
unnamed: D18.C, IC4.10 (0), RN4.2
unnamed: D19.C, IC4.11 (1), RN4.3
unnamed: D20.C, IC4.12 (2), RN4.4
unnamed: D2.C, D3.C, D4.A, IC2.5 (+IN)
unnamed: D21.C, IC4.13 (3), RN4.5
unnamed: D22.C, IC4.1 (4), RN4.9
unnamed: D23.C, IC4.2 (5), RN4.8
unnamed: D5.C, D6.C, D7.A, IC2.7 (+IN)
unnamed: D8.C, D9.C, D10.A, IC3.5 (+IN)
unnamed: D11.C, D12.C, D13.A, IC3.7 (+IN)
unnamed: D14.C, D15.C, D16.A, IC3.9 (+IN)
unnamed: D24.C, IC4.3 (6), RN4.7
unnamed: D25.C, IC4.4 (7), RN4.6
unnamed: IC1.1 (PC6(/RESET)), R12.2
unnamed: Q1.3 (C), R10.1
unnamed: D26.A, Q1.2 (B), R11.2
REVERSE: D28.C, IC6.10 (2C0), RN2.3
SELECT: A5.V (18), A6.V (18), R10.2
SHIELD1: A2.JJ (30), A2.V (18), A3.JJ (30), A3.V (18)
SHIELD2: A2.NN (34), A3.NN (34), B2.L (10), B2.Y (21), B3.L (10), B3.Y (21)
SKEW: A2.F (6), A3.F (6)
STOP: D29.C, IC5.6 (1C0), RN2.4
TIMING+: A2.K (9), A3.K (9), D2.A, R3.1
TIMING-: A2.R (14), A3.R (14), D3.A
TIMINGCT: A2.M (11), A3.M (11), D4.C, IC2.4 (-IN)
TIN: IC1.6 (PD4(XCK/T0)), IC2.2 (OUT), RN3.8
TOUT: IC1.18 (PB4(MISO)), R3.2
V+: C8.1, C9.1, IC2.3 (V+), IC3.3 (V+), R8.2
VCC: +5V.1, C2.+, C4.1, C5.1, C6.1, C7.1, IC1.7 (VCC), IC1.20 (AVCC), IC1.21 (AREF), IC4.16 (VCC), IC5.16 (VCC), IC6.16 (VCC), R1.2, R8.1, R12.1, RN2.1, RN3.1, RN4.1
VDD: C1.1, D1.C, J1.4 (VDD), R1.1
VSS: J1.3 (VSS), J1.6 (VSS), R2.1
WE: A5.W (19), A6.W (19), D17.A, D31.A, R9.2

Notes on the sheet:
Drive Control
Heads
This odd pinout is designed to match up
with BC08J replacement cable paddles.
TODO:
TU56M Compatibility
DECtape Drive Emulation
J? CR0_BAR?

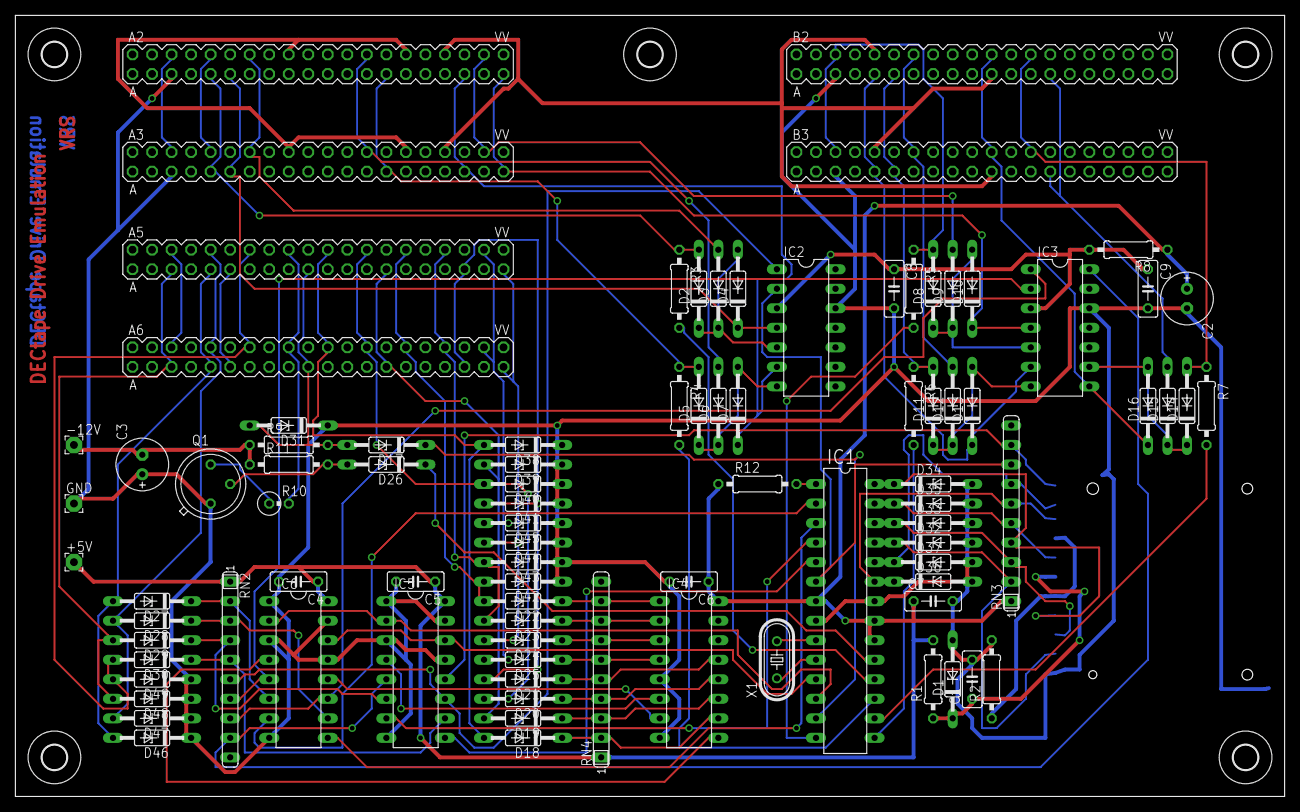
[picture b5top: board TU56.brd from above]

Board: 2 copper layers, 165.1 x 101.6 mm, 96 parts (1 on the bottom side), 91 nets.

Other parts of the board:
U$1, U$2, U$3, U$4, U$5: 3,2
